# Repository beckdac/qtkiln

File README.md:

# qtkiln
Open source controller for kilns with home assisstant integration

`wifi_cred.h` should look something like:
```
#define WIFI_SSID "ssid"
#define WIFI_PASS "password"
```

`mqtt_cred.h` should look something like:
```
#define MQTT_BROKER "192.168.1.42"
#define MQTT_USER "qtkiln"
#define MQTT_PASS "password"
#define MQTT_PORT 1883
```

Using `mosquitto` pub and sub clients on linux, you can modify the settings and listen to the devices, e.g.:
```
# listen to all traffic from kilns
mosquitto_sub -v -u mqtt_user -P mqtt_password -h mqtt_host -p 1883 -t 'qtkiln/#'
# change the config for a kiln and reset it
# for example, change the mqtt update frequency to once per 3 seconds
mosquitto_pub -L mqtt://mqtt_user:mqtt_password@mqtt_host/qtkiln/ECDA3BC01AB4/config -m '{"mqttUpdateInterval_ms":3000}'
mosquitto_pub -L mqtt://mqtt_user:mqtt_password@mqtt_host/qtkiln/ECDA3BC01AB4/config -m '{"reset":true}'
# change the set point for the temperature control
mosquitto_pub -L mqtt://mqtt_user:mqtt_password@mqtt_host/qtkiln/ECDA3BC01AB4/set -m '{"targetTemp_C":42}'
# turn on the pid control
mosquitto_pub -L mqtt://mqtt_user:mqtt_password@mqtt_host/qtkiln/ECDA3BC01AB4/set -m '{"pidEnabled":1}'
//mosquitto_pub -L mqtt://mqtt_user:mqtt_password@mqtt_host/qtkiln/ECDA3BC01AB4/get -m '{"targetTemp_C"}'
mosquitto_pub -L mqtt://mqtt_user:mqtt_password@mqtt_host/qtkiln/ECDA3BC01AB4/get -m 'statistics'
```

### Debug / test protocol
```
mosquitto_pub -L mqtt://mqtt_user:mqtt_password@mqtt_host/qtkiln/ECDA3BC01AB4/config -m '{"reset":true}'
mosquitto_pub -L mqtt://mqtt_user:mqtt_password@mqtt_host/qtkiln/ECDA3BC01AB4/config -m '{"mqttUpdateInterval_ms":3000}'
mosquitto_pub -L mqtt://mqtt_user:mqtt_password@mqtt_host/qtkiln/ECDA3BC01AB4/config -m '{"save":true}'
mosquitto_pub -L mqtt://mqtt_user:mqtt_password@mqtt_host/qtkiln/ECDA3BC01AB4/set -m '{"targetTemp_C":42}'
mosquitto_pub -L mqtt://mqtt_user:mqtt_password@mqtt_host/qtkiln/ECDA3BC01AB4/set -m '{"targetTemp_C":42,"pidEnabled":true}'
mosquitto_pub -L mqtt://mqtt_user:mqtt_password@mqtt_host/qtkiln/ECDA3BC01AB4/get -m '{"statistics":true}'
mosquitto_pub -L mqtt://mqtt_user:mqtt_password@mqtt_host/qtkiln/ECDA3BC01AB4/set -m '{"debugPriority":100}'
mosquitto_pub -L mqtt://mqtt_user:mqtt_password@mqtt_host/qtkiln/ECDA3BC01AB4/set -m '{"alarmOnSSR":true}'
mosquitto_pub -L mqtt://mqtt_user:mqtt_password@mqtt_host/qtkiln/ECDA3BC01AB4/set -m '{"pidEnabled":false}'
```

### Current dependency set:
```
  WiFi at version 3.1.3
  Networking at version 3.1.3
  Preferences at version 3.1.3
  MAX31855_RT at version 0.6.1
  SPI at version 3.1.3
  EspMQTTClientFork at version 1.13.4
  ArduinoOTA at version 3.1.3
  Update at version 3.1.3
  PubSubClient at version 2.8
  WebServer at version 3.1.3
  FS at version 3.1.3
  ESPmDNS at version 3.1.3
  TM1637 at version 1.2.0
  ArduinoJson at version 7.3.1
  QuickPID at version 3.1.9
  sTune at version 2.4.0
```

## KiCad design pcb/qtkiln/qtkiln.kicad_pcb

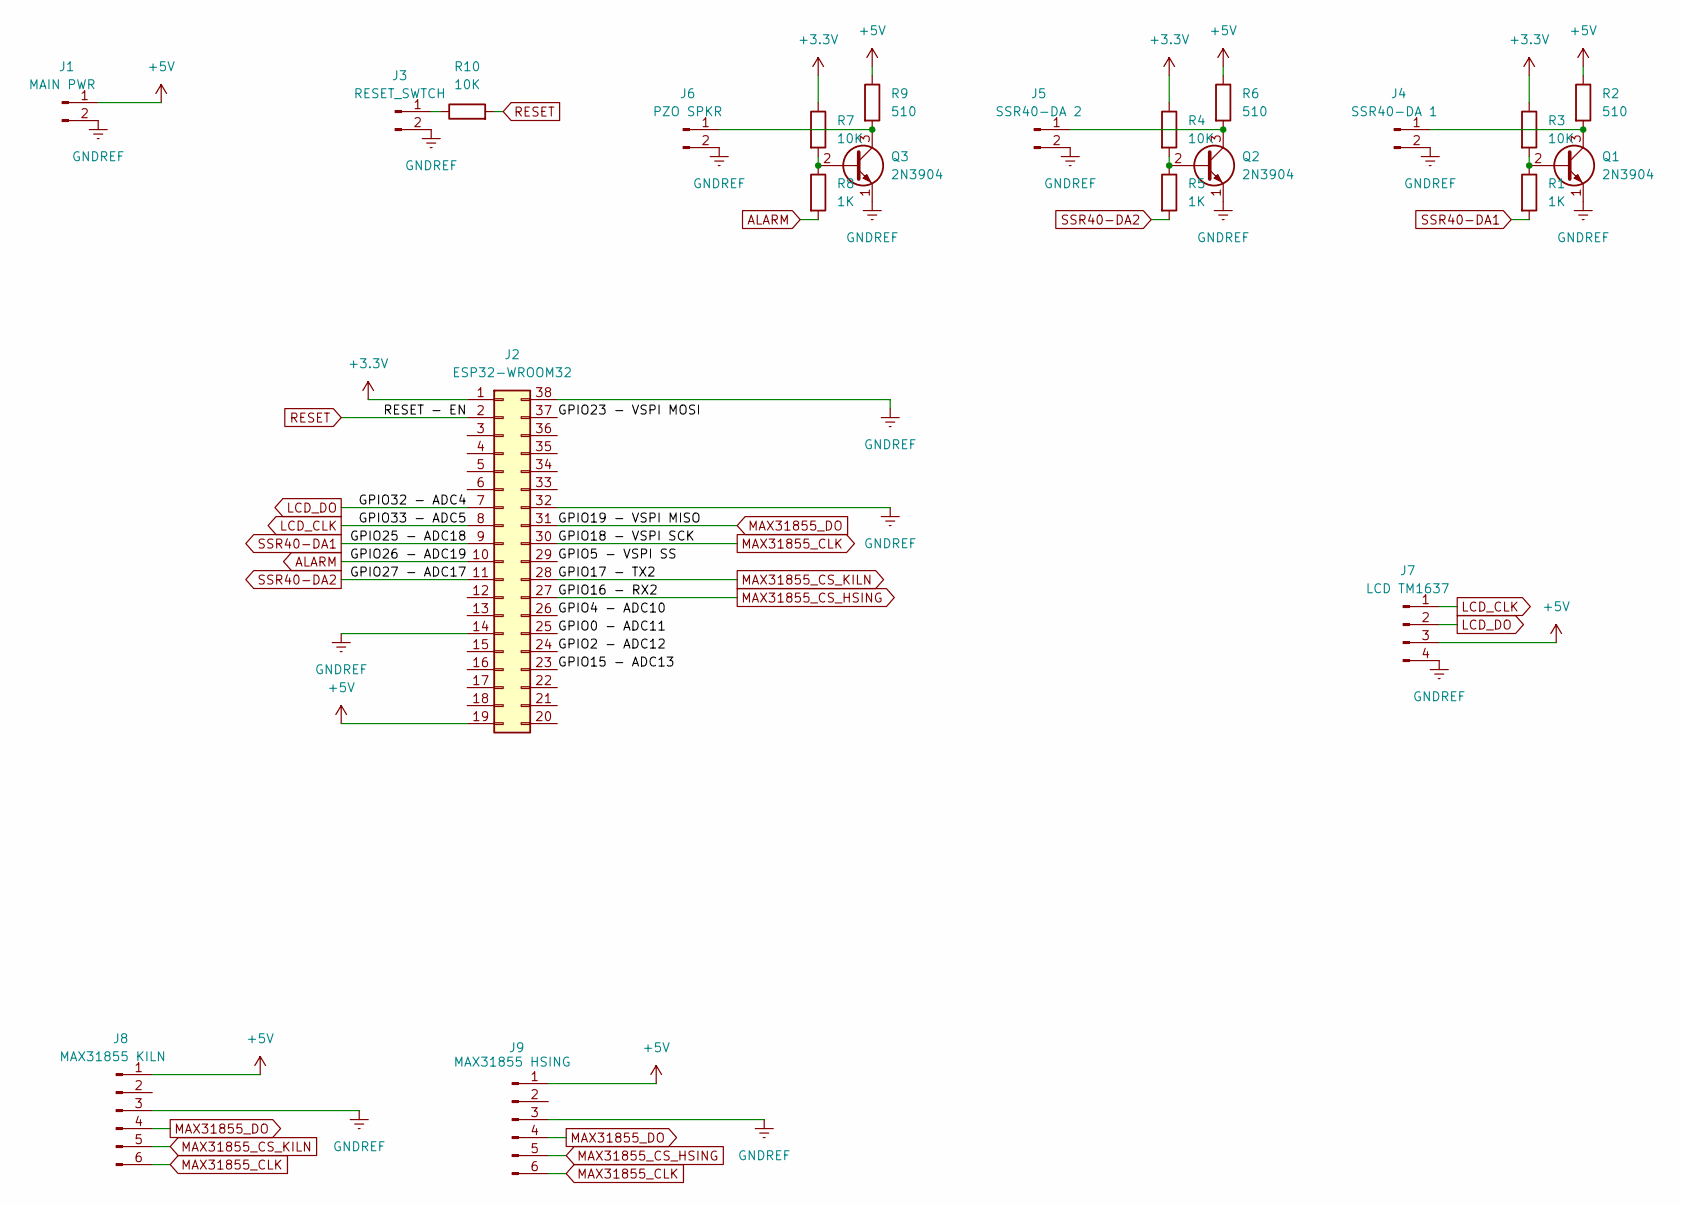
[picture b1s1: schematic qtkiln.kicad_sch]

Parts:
J1: MAIN_PWR; PinHeader_1x02_P2.54mm_Vertical
J2: ESP32_WROOM32; ESP32-DevKitC
J3: RESET_SWTCH; PinSocket_1x02_P2.54mm_Vertical
J4: SSR40_DA1; PinHeader_1x02_P2.54mm_Vertical
J5: SSR40_DA2; PinHeader_1x02_P2.54mm_Vertical
J6: PZO_SPKR; PinHeader_1x02_P2.54mm_Vertical
J7: LCD_TM1637; PinHeader_1x04_P2.54mm_Vertical
J8: MAX31855_KILN; PinSocket_1x06_P2.54mm_Vertical
J9: MAX31855_HSING; PinSocket_1x06_P2.54mm_Vertical
Q1, Q2, Q3: 2N3904; TO-92_Inline_Wide
R1, R5, R8: 1K; R_Axial_DIN0204_L3.6mm_D1.6mm_P5.08mm_Vertical
R2, R6, R9: 510; R_Axial_DIN0204_L3.6mm_D1.6mm_P5.08mm_Vertical
R3, R4, R7, R10: 10K; R_Axial_DIN0204_L3.6mm_D1.6mm_P5.08mm_Vertical

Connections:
+3.3V: J2.1, R3.1, R4.1, R7.1
+5V: J1.1, J2.19, J7.3, J8.1, J9.1, R2.1, R6.1, R9.1
/GPIO0 - ADC11: J2.25
/GPIO2 - ADC12: J2.24
/GPIO4 - ADC10: J2.26
/GPIO5 - VSPI SS: J2.29
/GPIO15 - ADC13: J2.23
/GPIO23 - VSPI MOSI: J2.37
ALARM: J2.10, R8.2
GNDREF: J1.2, J2.14, J2.32, J2.38, J3.2, J4.2, J5.2, J6.2, J7.4, J8.3, J9.3, Q1.1 (E), Q2.1 (E), Q3.1 (E)
LCD_CLK: J2.8, J7.1
LCD_DO: J2.7, J7.2
MAX31855_CLK: J2.30, J8.6, J9.6
MAX31855_CS_HSING: J2.27, J9.5
MAX31855_CS_KILN: J2.28, J8.5
MAX31855_DO: J2.31, J8.4, J9.4
unnamed: J3.1, R10.1
unnamed: J4.1, Q1.3 (C), R2.2
unnamed: J5.1, Q2.3 (C), R6.2
unnamed: J6.1, Q3.3 (C), R9.2
unnamed: Q1.2 (B), R1.1, R3.2
unnamed: Q2.2 (B), R4.2, R5.1
unnamed: Q3.2 (B), R7.2, R8.1
RESET: J2.2, R10.2
SSR40-DA1: J2.9, R1.2
SSR40-DA2: J2.11, R5.2

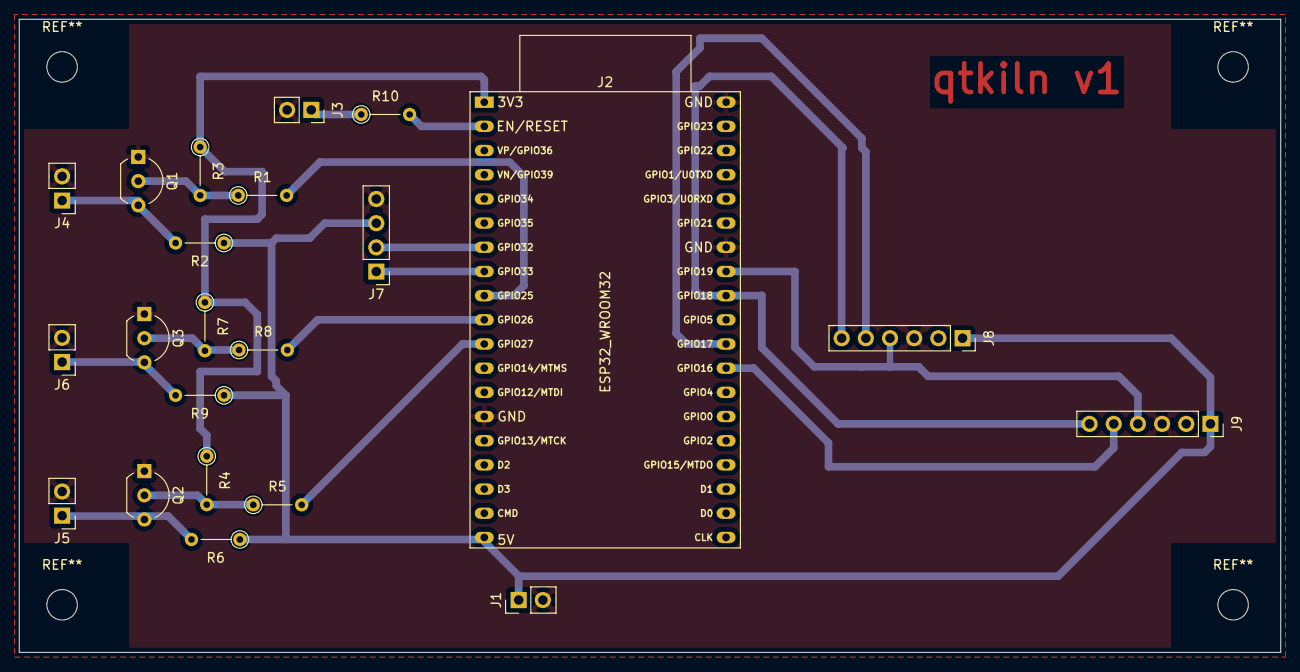
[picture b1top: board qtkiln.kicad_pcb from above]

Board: 2 copper layers, 132.5 x 66.5 mm, 22 parts (0 on the bottom side), 20 nets.

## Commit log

2025-03-16 prototype w/ out creds
2025-03-16 adding basic setup
2025-03-16 added some basic instrumentation on the main loop to see if we can avoid real time
2025-03-16 simplifying loop to remove iterations
2025-03-16 simple loop finished
2025-03-16 simple loop dox
2025-03-16 cleanup of config and other code
2025-03-16 added more docs
2025-03-16 adding pwm via a new library
2025-03-16 proof that early optimizations are useless
2025-03-16 when its been a minute since I wrote c++
2025-03-16 moved creds out of ino for mqtt
2025-03-16 added mqtt support
2025-03-16 cleanup of mqtt code in progress
2025-03-16 continued code cleanup and style into dacb
2025-03-16 back to ANSI
2025-03-16 settable update freqs across info bands
2025-03-16 more code cleanup and message simplification
2025-03-16 moving to independent thermo update, really rtoss isn't easier at this point?
2025-03-16 working towards full implqmentation
2025-03-16 syntax fixes, untested build
2025-03-16 changing mqtt message to include the last update time in ms
2025-03-16 match the call of the library
2025-03-16 its good to make functions return stuff
2025-03-16 cleanup of the thermo object
2025-03-16 buildable prototype
2025-03-16 added support for reading prefs
2025-03-16 time to eat something this weekend
2025-03-16 using prefs that cna be set via mqtt
2025-03-16 working prototype
2025-03-16 working on having a set point for pid target
2025-03-16 added some docs because I forget
2025-03-16 internally managed pwm and pid using new lib
2025-03-16 starting kiln pid from old foundry values
2025-03-16 removed bad prototypes
2025-03-16 resolved functions
2025-03-16 resolved misnamed functions
2025-03-16 improving serial debugging
2025-03-16 clean up repetitive calls in the same state
2025-03-16 working prototype again
2025-03-16 working real time pid tunings
2025-03-17 working towards practical pid
2025-03-17 updated docs
2025-03-17 adding in additional information probing support
2025-03-17 fixed up some variable names
2025-03-17 docs and wrong func name
2025-03-17 fixed up output format
2025-03-17 fixed output for % of time
2025-03-17 working lcd
2025-03-17 i/o fixes
2025-03-17 working towards two different phy
2025-03-17 working towards two different phy colon
2025-03-17 place holders
2025-03-18 moving to a json format for io and prefs
2025-03-18 working json for prefs
2025-03-18 prototypes but ignored for now
2025-03-18 moving defines out
2025-03-18 updating docs
2025-03-18 fixing up the settings for all json
2025-03-18 fixed regulation
2025-03-18 variable refactoring
2025-03-18 more refactoring for names and layout
2025-03-18 fixed types in examples
2025-03-18 more refactoring
2025-03-18 fixed potential out of bounds
2025-03-18 added config for turning on and off debug for mqtt to serial
2025-03-18 almost working, but not every cycle goes off
2025-03-18 removed extra serial print
2025-03-19 stubs of program infra
2025-03-20 working towards rtos
2025-03-20 updated rtos for thermo, working
2025-03-20 fixed issue with updates not being propagated to object tasks
2025-03-20 fixed up some compile fails, but this versio segfaults
2025-03-20 working tasks for thermo and program
2025-03-20 fixed up allocation and memory
2025-03-20 moving towards complete rtos
2025-03-20 moving towards encapsulating pid in pwm
2025-03-20 continued syntax corrections
2025-03-20 buildable binary w/ rtos for all major components
2025-03-20 final round of syntax fixes
2025-03-20 fixed up some minor compilation issues with statistics
2025-03-22 pid+tasks+info+bigmqttbuffer=working
2025-03-22 PID fault detection
2025-03-22 mqtt logging
2025-03-22 working program upload
2025-03-22 support for loading and saving programs over mqtt
2025-03-22 temporary commit of mostly working low pass filter before ultimate game
2025-03-22 seemingly working low pass filter
2025-03-22 fixed up boot so the low pass filter has time to settle
2025-03-22 fixing up debug output for production
2025-03-22 loading programs from prefs
2025-03-23 safety interlock from physical prototype
2025-03-23 pausing because of hardware failure
2025-03-23 style fixed and moving alarm to get around boot pin issue
2025-03-24 alarm pin forcing
2025-03-25 max conversion and last nights fixes
2025-03-26 matching to new hardware
2025-03-26 clarity fixes, and work from debugging
2025-03-26 configuration settable by prefs for wifi and mqtt
2025-03-26 fixes to program storage key length
2025-03-26 added support for home assistant auto discovery, loading programs and reorganizing firmware task priority
2025-03-27 various fixes and phy reorg for real hardware
2025-03-27 enabled pwm when the program is turned on
2025-03-27 modified pid and added a restart capability, more debugging
2025-03-27 moving to QuickPID and sTune, adding testing alarm for ssr feature
2025-03-27 working towards auto tuning
2025-03-28 added support for live tuning
2025-03-28 first building version of auto tuning
2025-03-28 fixing up what is auto and manual where
2025-03-28 last commit before tuning rewrite
2025-03-28 added better docs for tuning protocol
2025-03-28 big refactor for pwm and pid that can be separated partly
2025-03-28 seemingly working auto tuning
2025-03-28 adding support for dynamic setting tuning parameters for multiple tunings
2025-03-28 add cleaner transition from state to out of state
2025-03-28 revisited basic pid for some more tuning
2025-03-28 runnable programs for testing
2025-03-29 improved information and debugging
2025-03-29 various informational fixes for programs and get functions
2025-03-29 small code cleanup and better debug handling
2025-03-29 added some basic program example
2025-03-29 fixed up memory allocation and bug in debug output
2025-03-30 simple refactor, code cleanup and major bug fix
2025-03-30 fixed a bug on MAX31855 error and other info fixes
2025-03-30 untested debugging and define name changes
2025-03-30 missed extern for reporting
2025-03-30 notebook for fitting out PID parameters from step test or response curve
2025-03-31 playing with some data for PID
2025-04-01 updating some experiments
2025-04-01 information fixes and management of alarms and errors
2025-04-01 fixed stray text in file
2025-04-01 slowed SPI for the thermo couples down to 1/4 (4mhz)
2025-04-01 updated with new data
2025-04-05 added home assistant integrations from old files
2025-04-06 working homeassistant integration
2025-04-19 fixing up docs
2025-04-19 revising ignore files to avoid data extracts
2025-04-19 revising file structure
2025-04-19 removing unused files
2025-04-28 additional examples
2025-04-29 added pcb and some basic milling code
2025-05-02 added image of pcb
2025-05-02 added support for second ssr controlled by additional pin
2025-05-02 updated pcb from latest milling
2025-05-02 added flatcam project and revised structure
2025-05-02 added link to PCB image
2025-05-03 improved home assistant integration with drop down program list
2025-05-04 move IP to sensor type and payload fix for pid and pwm for homeass
2025-05-04 finalized run program homeass integration
2025-05-04 added versioning support for reporting
